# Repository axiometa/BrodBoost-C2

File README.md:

# BrodBoost-C2

BrødBoost-C2 is a project of Axiometa, it is available for sale at [axiometa.io](https://www.axiometa.io/products/axiometa-brodboost-c2-breadboard-power-supply)

BrødBoost-C2 is a USB-C breadboard power supply that delivers clean 5V and 3.3V power directly to your breadboard. It features short-circuit fuse protection, USB ESD protection, an ideal diode for reverse polarity safety, a load switch with soft startup, and ferrite bead filtering for low-noise operation. An on/off switch and power LED keep you in control, while USB data passthrough keeps your lines accessible.

# Overview

# Compatibility

# Voltage Selection
Both voltage rails can be independently selected or simultaneously set to 5.0 V or 3.3 V by moving around the jumper cap. Although the jumper cap design has received mixed opinions, it is implemented here as a safety feature and to be cautios of BOM. The design requires deliberate jumper cap movement, which helps prevent accidental voltage changes from 3.3 V to 5.0 V that might occur if a switch were used.

# Schematic
A USB-C receptacle accepts a standard USB-C cable. The CC1 and CC2 lines are pulled to ground through 5.1 kΩ resistors to negotiate 5 V from the host. Power flows through a ferrite bead for noise suppression, a 1 A polyfuse for short-circuit protection, and decoupling capacitors.
An ideal diode provides reverse polarity and overvoltage protection. A load switch with controlled soft startup prevents inrush current. The power switch and red power LED sit in series on the main rail. USB ESD protection is included on the data and power lines.
Step-down conversion from 5 V to 3.3 V is handled by the AP2114H-3.3TRG1 LDO regulator. Both voltage outputs are routed to 1×3 2.54 mm headers for rail selection. A separate header provides access to 5 V, 3.3 V, ground, and USB data lines.

# PCB Design
BrodBoost-C2 is a two-layer PCB measuring 12 mm by 54.0 mm, designed to maximize trace width and optimize the switching regulator's ground return path. This layout comfortably supports the nominal device current of approximately 1 A.

**Top**

**Bottom**

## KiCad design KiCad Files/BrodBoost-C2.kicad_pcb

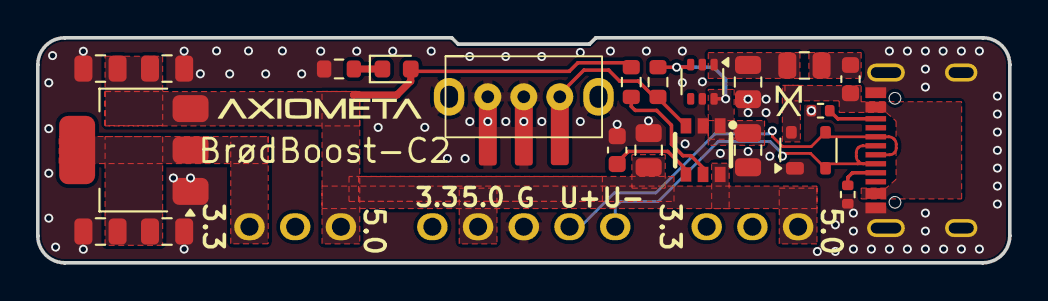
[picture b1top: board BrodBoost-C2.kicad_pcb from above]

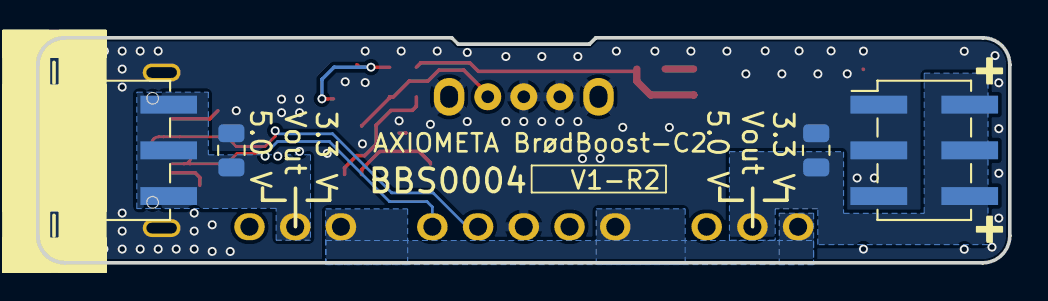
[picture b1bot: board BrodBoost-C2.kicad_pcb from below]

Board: 2 copper layers, 54.0 x 12.5 mm, 29 parts (4 on the bottom side), 17 nets.

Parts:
C1, C8, C13: 10uF; C_0805_2012Metric
C2, C4, C5: 10 uF; C_0805_2012Metric
C3, C7: 100nF; C_0805_2012Metric
C6: 10nF; C_0603_1608Metric
C14: 22uF; C_0805_2012Metric
D2: PRTR5V0U2X; SOT-143
D3: Red; LED_0603_1608Metric
F1: Polyfuse; Fuse_0603_1608Metric
FB1: C85840; C_0805_2012Metric
J1, J2: Conn_02x02_Counter_Clockwise; PinHeader_2x03_P2.54mm_Vertical_SMD
J3, J4: Select; PinHeader_1x03_P2.54mm_Vertical
J6: Breakout; PinHeader_1x05_P2.54mm_Horizontal
P1: C2909610; USB-C-16Pin-Orange
R3, R4: 5.1k; R_0402_1005Metric
R5, R10: 5.1k; R_0603_1608Metric
R6: 100; R_0603_1608Metric
U1: TPS22918
U2: Side Switch; TO-92_Inline_Wide
U3: AP2114HA-3.3TRG1; SOT-223-3_TabPin2
U10: LM66100DCK; SOT-363_SC-70-6

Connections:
+3V3: C7.1, C14.1, J3.1, J4.1, J6.1, U3.2 (VO)
+5V: C3.1, C5.1, C13.1, D3.2 (A), J3.3, J4.3, J6.2, R6.2, U1.6 (VOUT), U3.3 (VI)
/BB_NET_1: C1.2, J2.2, J2.4, J2.6, J3.2
/BB_NET_2: C8.2, J1.2, J1.4, J1.6, J4.2
/CC1: P1.A5 (CC1), R4.2
/CC2: P1.B5 (CC2), R3.2
/USB+: D2.3 (I/O2), J6.4, P1.A6 (DP1), P1.B6 (DP2)
/USB-: D2.2 (I/O1), J6.5, P1.A7 (DN1), P1.B7 (DN2)
/V_BUS: D2.4 (VCC), F1.1, P1.A4B9 (VBUS), P1.B4A9 (VBUS)
GND: C1.1, C2.2, C3.2, C4.2, C5.2, C6.2, C7.2, C8.1, C13.2, C14.2, D2.1 (GND), J1.1, J1.3, J1.5, J2.1, J2.3, J2.5, J6.3, P1.12, P1.13, P1.14, P1.15, P1.A1B12 (GND), P1.B1A12 (GND), R3.1, R4.1, R10.2, U1.2 (GND), U2.3, U3.1 (GND), U10.2 (GND), U10.5 (ST)
unnamed: D3.1 (K), R10.1
unnamed: F1.2, FB1.1
unnamed: C6.1, U1.4 (CT)
unnamed: R5.2, U1.3 (ON), U2.5
unnamed: R6.1, U1.5 (QOD)
unnamed: C4.1, R5.1, U1.1 (VIN), U10.3 (~CE), U10.6 (VOUT)
unnamed: C2.1, FB1.2, U10.1 (VIN)

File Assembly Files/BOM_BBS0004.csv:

Designator,Footprint,Quantity,Value,LCSC Part #,
"C13,C8,C1",805,3,10uF,C15850,
C14,805,1,22uF,C45783,
"C2, C4, C5",805,3,10 uF,C15850,
"C3, C7",805,2,100nF,C49678,
C6,603,1,10nF,C57112,
D2,SOT-143,1,PRTR5V0U2X,C5158049,
D3,603,1,Red,C965799,
F1,603,1,Polyfuse,C18203128,
FB1,805,1,Ferrite Bead,C85840,
"J1, J2",PinHeader_2x03_P2.54mm_Vertical_SMD,2,Bottom,C3294461,
"J3, J4",PinHeader_1x03_P2.54mm_Vertical,2,Select,C5360899,
P1,USB-C-16Pin,1,,C2927038,
"R10, R5",603,2,5.1k,C23186,
"R3, R4",402,2,5.1k,C25905,
R6,603,1,100,C22775,
U1,TPS22918,1,TPS22918,C131941,
U10,SOT-363_SC-70-6,1,LM66100DCK,C2869734,
U2,on/off switch,on/off switch,on/off switch,C2939725,or side: C50878478
U3,SOT-223-3_TabPin2,1,AP2114H-3.3TRG1,C150716,

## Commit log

2026-04-06 Added Read Me
2026-04-06 Add images for top and bottom PCB design
2026-04-06 added license
